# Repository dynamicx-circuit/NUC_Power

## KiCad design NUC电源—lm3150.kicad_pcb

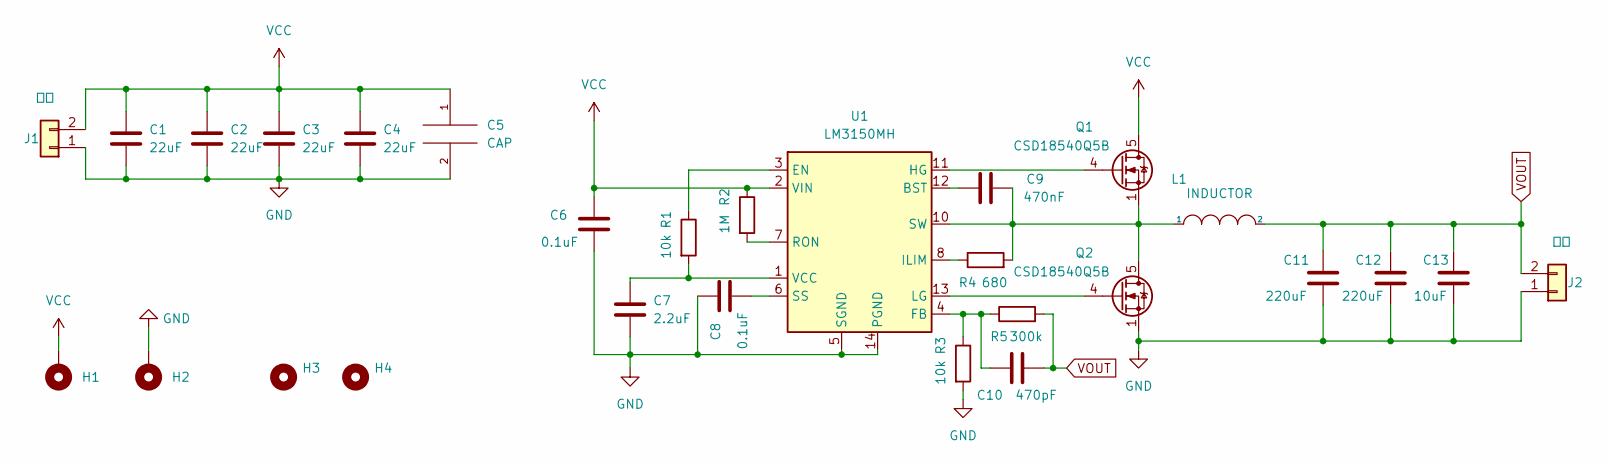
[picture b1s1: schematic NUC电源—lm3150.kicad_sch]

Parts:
C1, C2, C3, C4: 22uF; C_1206_3216Metric_Pad1.33x1.80mm_HandSolder
C5: CAP; C_Elec_8x10.2
C6, C8: 0.1uF; C_0603_1608Metric_Pad1.08x0.95mm_HandSolder
C7: 2.2uF; C_0603_1608Metric_Pad1.08x0.95mm_HandSolder
C9: 470nF; C_0603_1608Metric_Pad1.08x0.95mm_HandSolder
C10: 470pF; C_0603_1608Metric_Pad1.08x0.95mm_HandSolder
C11, C12: 220uF; C_Elec_8x10.2
C13: 10uF; C_1206_3216Metric_Pad1.33x1.80mm_HandSolder
H1, H2: MountingHole_Pad; MountingHole_2.2mm_M2_Pad_TopBottom
H3, H4: MountingHole; MountingHole_2.2mm_M2
J1: Conn_01x02; AMASS_XT30PW-M_1x02_P2.50mm_Horizontal
J2: Conn_01x02; AMASS_XT30PW-F_1x02_P2.50mm_Horizontal
L1: INDUCTOR; L_10.4x10.4_H4.8
Q1, Q2: CSD18540Q5B; TDSON-8-1
R1, R3: 10k; R_0603_1608Metric_Pad0.98x0.95mm_HandSolder
R2: 1M; R_0603_1608Metric_Pad0.98x0.95mm_HandSolder
R4: 680; R_0805_2012Metric_Pad1.20x1.40mm_HandSolder
R5: 300k; R_0603_1608Metric_Pad0.98x0.95mm_HandSolder
U1: LM3150MH; HTSSOP-14-1EP_4.4x5mm_P0.65mm_EP3.4x5mm_Mask3x3.1mm

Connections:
GND: C1.2, C2.2, C3.2, C4.2, C5.2, C6.2, C7.2, C8.1, C11.2, C12.2, C13.2, H2.1, J1.1, J2.1, Q2.1 (S), Q2.2 (S), Q2.3 (S), R3.2, U1.5 (SGND), U1.9 (SGND), U1.14 (PGND), U1.15 (SGND)
unnamed: C7.1, R1.2, U1.1 (VCC)
unnamed: C8.2, U1.6 (SS)
unnamed: C9.1, L1.1, Q1.1 (S), Q1.2 (S), Q1.3 (S), Q2.5 (D), R4.2, U1.10 (SW)
unnamed: C9.2, U1.12 (BST)
unnamed: C10.1, R3.1, R5.1, U1.4 (FB)
unnamed: Q1.4 (G), U1.11 (HG)
unnamed: Q2.4 (G), U1.13 (LG)
unnamed: R1.1, U1.3 (EN)
unnamed: R2.2, U1.7 (RON)
unnamed: R4.1, U1.8 (ILIM)
VCC: C1.1, C2.1, C3.1, C4.1, C5.1, C6.1, H1.1, J1.2, Q1.5 (D), R2.1, U1.2 (VIN)
VOUT: C10.2, C11.1, C12.1, C13.1, J2.2, L1.2, R5.2

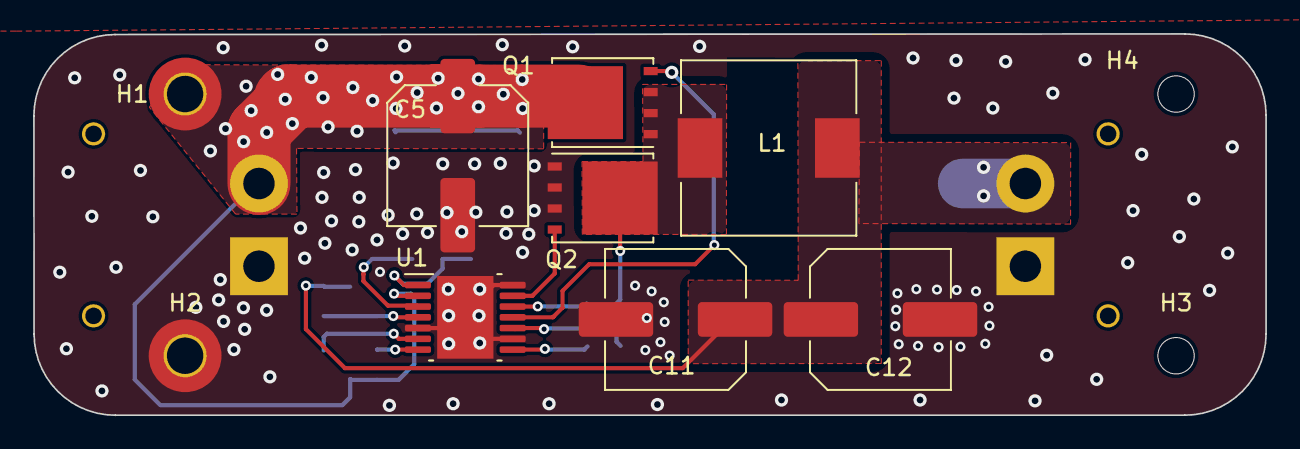
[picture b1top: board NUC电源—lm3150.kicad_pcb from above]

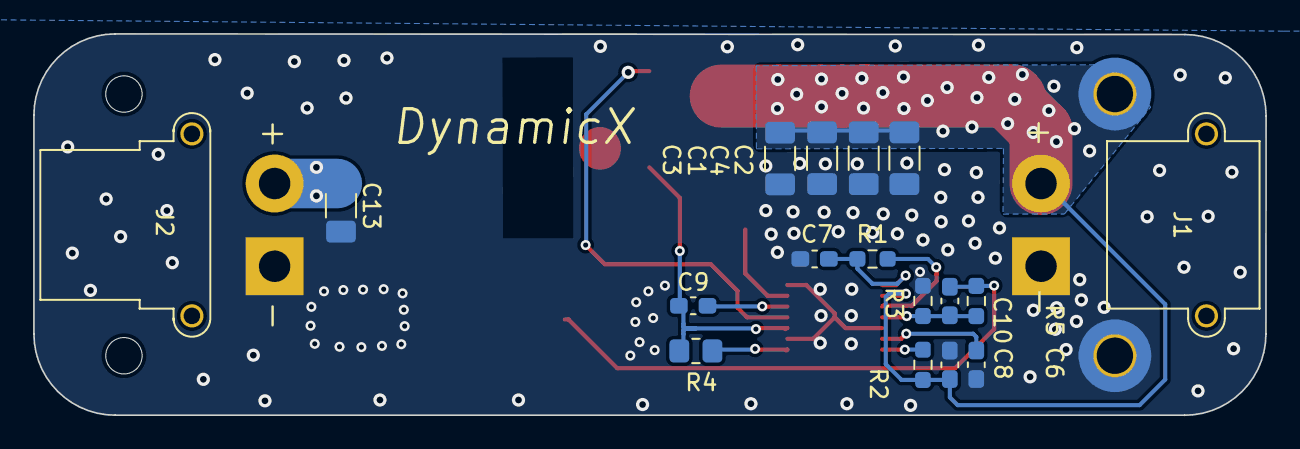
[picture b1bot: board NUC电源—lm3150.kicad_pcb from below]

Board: 2 copper layers, 74.5 x 23.0 mm, 28 parts (17 on the bottom side), 13 nets.

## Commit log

2022-10-10 Add NUC Power project
2022-10-10 Rename .gitignore
